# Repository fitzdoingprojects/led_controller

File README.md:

# led_controller
Led Controller, Arduino + Kicad

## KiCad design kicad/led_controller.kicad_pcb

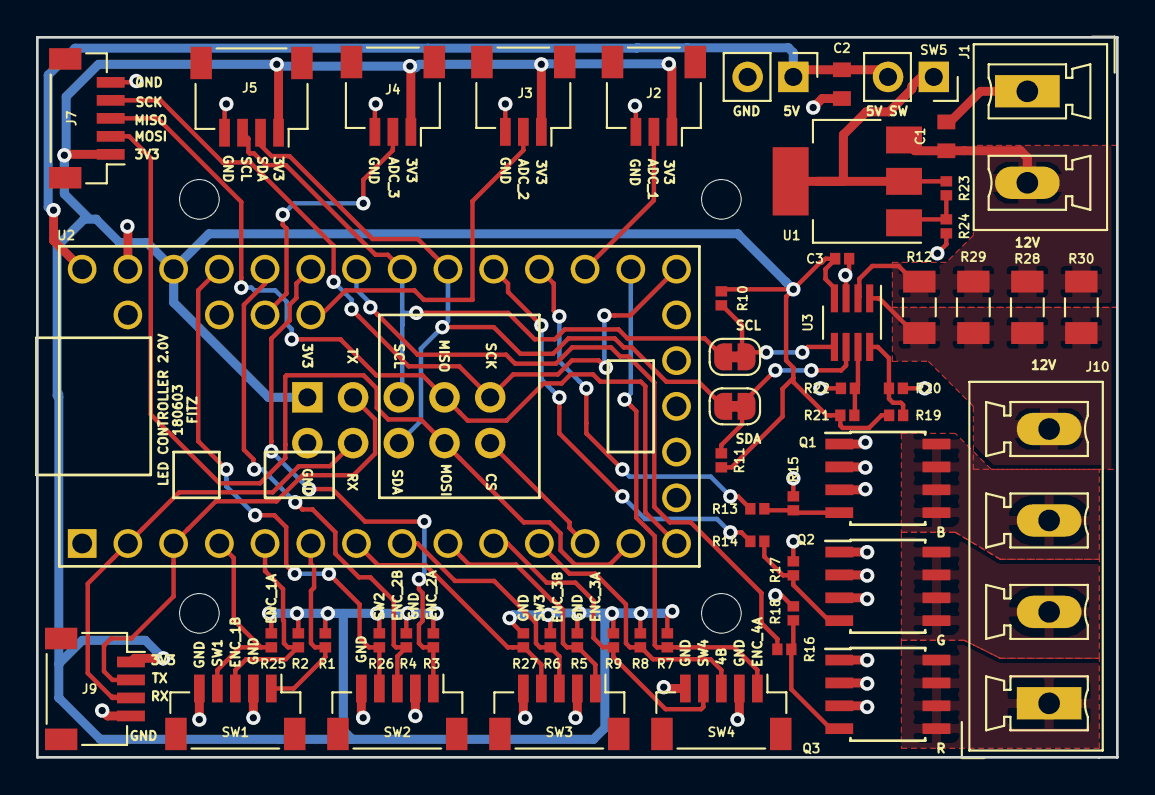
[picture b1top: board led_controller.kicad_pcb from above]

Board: 2 copper layers, 60.0 x 40.0 mm, 60 parts (1 on the bottom side), 43 nets.

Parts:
C1, C2: 10uF; C_0603_1608Metric
C3: 0.1uF; C_0402_1005Metric
J1: PWR_IN; PhoenixContact_MCV_1,5_2-G-5.08_1x02_P5.08mm_Vertical
J2: ADC1; JST_SH_SM03B-SRSS-TB_1x03-1MP_P1.00mm_Horizontal
J3: ADC2; JST_SH_SM03B-SRSS-TB_1x03-1MP_P1.00mm_Horizontal
J4: ADC3; JST_SH_SM03B-SRSS-TB_1x03-1MP_P1.00mm_Horizontal
J5: I2C; JST_SH_SM04B-SRSS-TB_1x04-1MP_P1.00mm_Horizontal
J6: UEXT; PinHeader_2x05_P2.54mm_Vertical
J7: SPI; JST_SH_BM05B-SRSS-TB_1x05-1MP_P1.00mm_Vertical
J8: 5V; Pin_Header_Straight_1x02_Pitch2.54mm
J9: UART; JST_SH_SM04B-SRSS-TB_1x04-1MP_P1.00mm_Horizontal
J10: Conn_01x04; PhoenixContact_MCV_1,5_4-G-5.08_1x04_P5.08mm_Vertical
JP1, JP2: Jumper_NC_Small; SolderJumper-2_P1.3mm_Bridged_RoundedPad1.0x1.5mm
MK1, MK2, MK3, MK4: Mounting_Hole; MountingHole_2.2mm_M2
Q1, Q2, Q3: IRF8721PBF-1; SOIC-8_3.9x4.9mm_Pitch1.27mm
R1, R2, R3, R4, R5, R6, R7, R8, R9, R10, R11, R15, R17, R18, R19, R20, R21, R22, R23, R24, R25, R26, R27: 10K; R_0402_1005Metric
R12, R28, R29, R30: 0R1; R_1206_3216Metric
R13, R14, R16: 100R; R_0402_1005Metric
SW1, SW2, SW3, SW4: Rotary_Encoder_Switch; JST_SH_BM05B-SRSS-TB_1x05-1MP_P1.00mm_Vertical
SW5: SW_DIP_x01; PinSocket_1x02_P2.54mm_Vertical
U1: AP1117-ADJ; SOT-223-3_TabPin2
U2: Teensy-LC; Teensy30_31_32_LC
U3: INA219; SOT-23-8_Handsoldering

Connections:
+3V3: C3.1, J2.1, J3.1, J4.1, J5.1, J6.1, J7.1, J9.1, R1.2, R2.2, R3.2, R4.2, R5.2, R6.2, R7.2, R8.2, R9.2, R10.1, R11.1, R19.1, R21.1, R25.2, R26.2, R27.2, U2.31, U3.4
+5V: C2.1, J8.1, SW5.2, U2.33
+12V: C1.1, J1.2, R12.1, R28.1, R29.1, R30.1, U1.3, U3.2
/5V_SW: R23.1, SW5.1, U1.2
/12V_SHUNT: J10.4, R12.2, R28.2, R29.2, R30.2, U3.1
/ADC_1: J2.2, U2.22
/ADC_2: J3.2, U2.37
/ADC_3: J4.2, U2.36
/CS0: J6.10, U2.12
/ENC_1A: R1.1, SW1.1, U2.6
/ENC_1B: R2.1, SW1.3, U2.5
/ENC_2A: R3.1, SW2.1, U2.28
/ENC_2B: R4.1, SW2.3, U2.29
/ENC_3A: R5.1, SW3.1, U2.9
/ENC_3B: R6.1, SW3.3, U2.8
/ENC_4A: R7.1, SW4.1, U2.21
/ENC_4B: R8.1, SW4.3, U2.11
/MISO0: J6.7, J7.3, U2.14
/MOSI0: J6.8, J7.2, U2.13
/OUT_B: J10.3, Q1.5, Q1.6, Q1.7, Q1.8
/OUT_G: J10.2, Q2.5, Q2.6, Q2.7, Q2.8
/OUT_R: J10.1, Q3.5, Q3.6, Q3.7, Q3.8
/PWM_B: R13.1, U2.23
/PWM_G: R14.1, U2.24
/PWM_R: R16.1, U2.27
/RX: J6.4, J9.3, U2.2
/SCK0: J6.9, J7.4, U2.20
/SCL: J5.3, J6.5, JP2.2, U2.26
/SDA: J5.2, J6.6, JP1.2, U2.25
/SW1: R25.1, SW1.4, U2.4
/SW2: R26.1, SW2.4, U2.30
/SW3: R27.1, SW3.4, U2.7
/SW4: R9.1, SW4.4, U2.10
/TX: J6.3, J9.2, U2.3
GND: C1.2, C2.2, C3.2, J1.1, J2.3, J3.3, J4.3, J5.4, J6.2, J7.5, J8.2, J9.4, Q1.1, Q1.2, Q1.3, Q2.1, Q2.2, Q2.3, Q3.1, Q3.2, Q3.3, R15.2, R17.2, R18.2, R20.2, R22.2, R24.2, SW1.2, SW1.5, SW2.2, SW2.5, SW3.2, SW3.5, SW4.2, SW4.5, U2.17, U2.32, U3.3
unnamed: JP1.1, R11.2, U3.6
unnamed: JP2.1, R10.2, U3.5
unnamed: Q1.4, R13.2, R15.1
unnamed: Q2.4, R14.2, R17.1
unnamed: Q3.4, R16.2, R18.1
unnamed: R19.2, R20.1, U3.8
unnamed: R21.2, R22.1, U3.7
unnamed: R23.2, R24.1, U1.1

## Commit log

2017-10-18 added .gitignore
2017-10-18 first board layout
2018-01-18 added arduino libraries
2018-02-23 added stobe and fixed a bunch of bugs
2018-03-18 saves board state, before teensy update
2018-05-31 switches to kicad and updates schematic and footprints
2018-06-01 finishes placement and power routing
2018-06-02 finishes layout, needs look over and silk
2018-06-04 final commit before seeed, adds gerbers
